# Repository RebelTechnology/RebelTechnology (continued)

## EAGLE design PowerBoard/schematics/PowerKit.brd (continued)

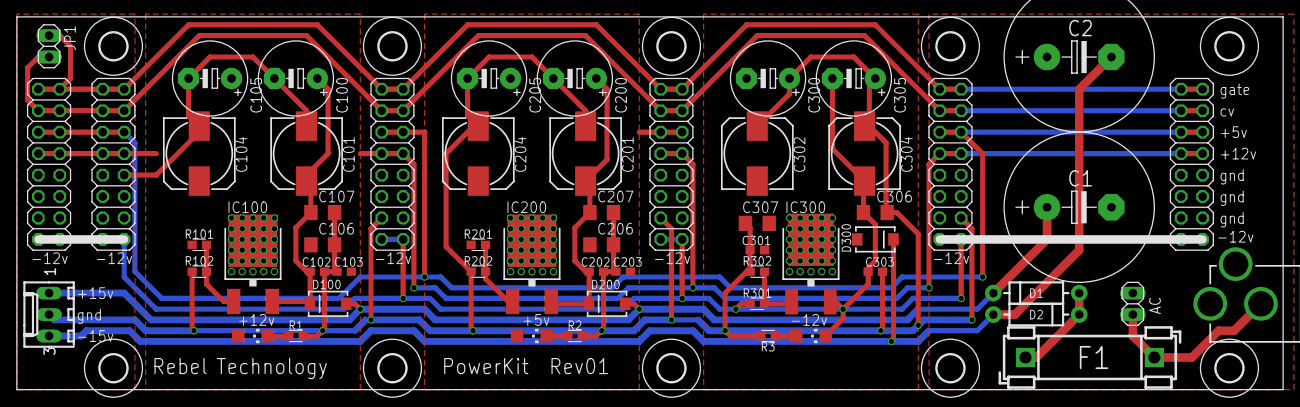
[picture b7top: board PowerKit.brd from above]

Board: 2 copper layers, 149.9 x 44.1 mm, 67 parts (0 on the bottom side), 19 nets.

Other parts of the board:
U$1, U$2, U$3, U$4, U$5, U$6, U$7, U$8, U$12, U$13: 3,2

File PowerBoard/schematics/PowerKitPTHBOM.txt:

Partlist exported from D:/Drive/Work/Rebel/ProjectFiles/RebelTechnology/PowerBoard/schematics/PowerKitPTH.sch at 14/04/2015 16:49:12

Qty Value            Device           Package            Parts                                                Description                                         
3                    LED3MM           LED3MM             LED1, LED2, LED3                                     LED                                                 
2                    PINHD-1X2        1X02               AC, JP1                                              PIN HEADER                                          
1                    POWER_JACKPTH    POWER_JACK_PTH     J1                                                   Power Jack                                          
6   100n             C-EU050-025X075  C050-025X075       C101, C103, C201, C203, C301, C303                   CAPACITOR, European symbol                          
9   10u              CPOL-EUE2.5-6    E2,5-6             C100, C102, C104, C200, C202, C204, C300, C302, C304 POLARIZED CAPACITOR, European symbol                
3   1N4004           1N4004           DO41-10            D100, D200, D300                                     DIODE                                               
2   1N5404           DIODE1N4001      DIODE-1N4001       D1, D2                                               Diode                                               
1   1k               R-EU_0204/7      0204/7             R202                                                 RESISTOR, European symbol                           
1   1k               R-EU_0207/7      0207/7             R2                                                   RESISTOR, European symbol                           
2   1k91             R-EU_0204/7      0204/7             R102, R302                                           RESISTOR, European symbol                           
1   22-27-2031-03    22-27-2031-03    6410-03            X1                                                   CONNECTOR                                           
1   2200u            CPOL-EUE7.5-18   E7,5-18            C2                                                   POLARIZED CAPACITOR, European symbol                
2   220R             R-EU_0204/7      0204/7             R101, R301                                           RESISTOR, European symbol                           
2   2k               R-EU_0207/7      0207/7             R1, R3                                               RESISTOR, European symbol                           
1   330R             R-EU_0204/7      0204/7             R201                                                 RESISTOR, European symbol                           
1   337T             337T             TO220H             IC300                                                Negative VOLTAGE REGULATOR                          
1   4700u            CPOL-EUE7.5-18   E7,5-18            C1                                                   POLARIZED CAPACITOR, European symbol                
1   FUSEBLANK_5X20MM FUSEBLANK_5X20MM FUSE_HOLDER_5X20MM F1                                                   Fuse                                                
2   LM317MABT        LM317MABT        TO220L1            IC100, IC200                                         500 mA Adjustable Output Positive Voltage Regulator 
6   M08X2            M08X2            2X8                OUT, OUT1, OUT2, OUT3, OUT4, OUT5

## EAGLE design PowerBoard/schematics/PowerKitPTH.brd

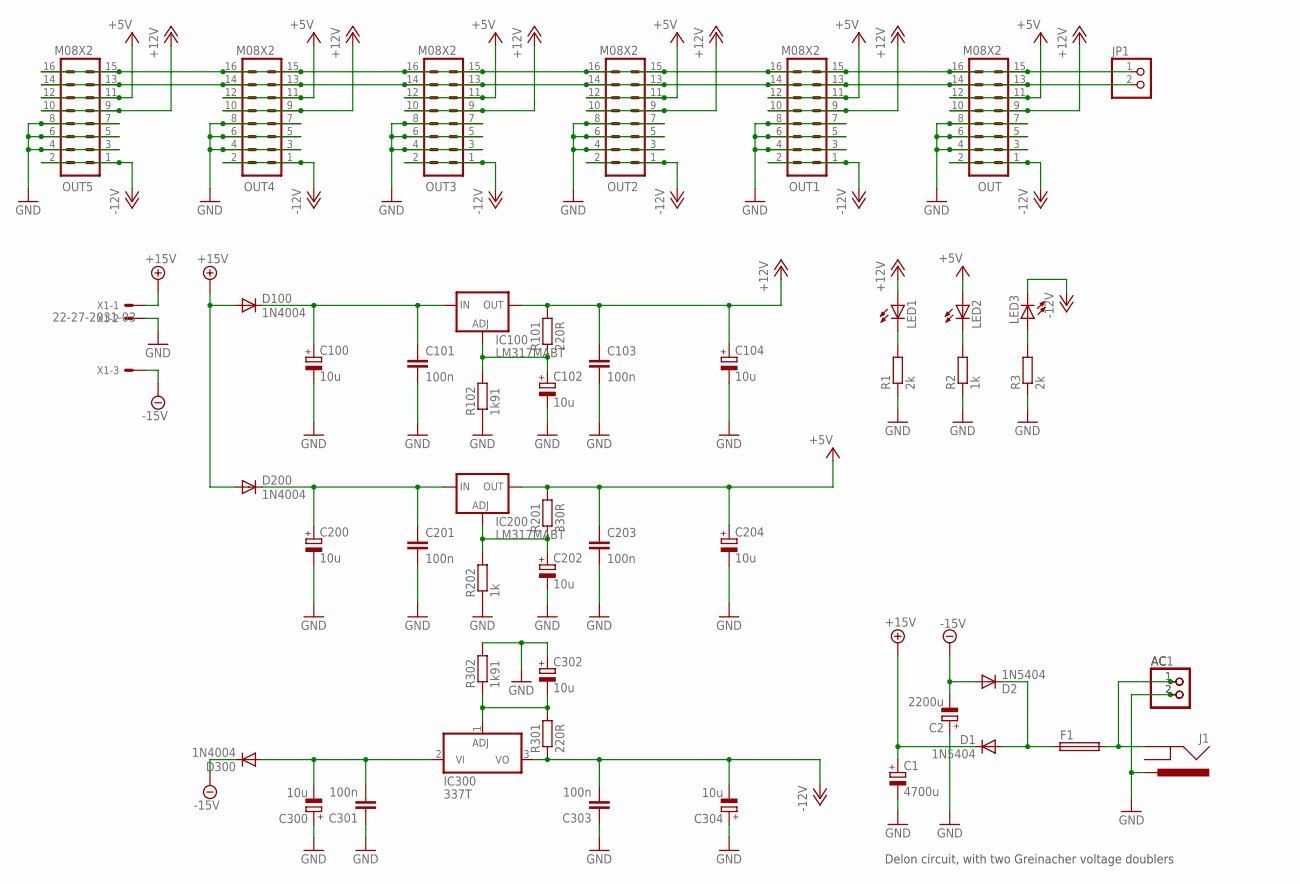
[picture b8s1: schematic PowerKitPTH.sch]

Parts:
AC, AC1: PINHD-1X2; 1X02
C1: 4700u; E7,5-18
C2: 2200u; E7,5-18
C100, C102, C104, C200, C202, C204, C300, C302, C304: 10u; E2,5-6
C101, C103, C201, C203, C301, C303: 100n; C050-025X075
D1, D2: 1N5404; DIODE-1N4001
D100, D200, D300: 1N4004; DO41-10
F1: SH22,5
IC100, IC200: LM317MABT; TO220L1
IC300: 337T; TO220H
J1: POWER_JACKPTH; POWER_JACK_PTH
JP1: PINHD-1X2; 1X02
LED1, LED2, LED3: LED3MM
OUT, OUT1, OUT2, OUT3, OUT4, OUT5: M08X2; 2X8
R1, R3: 2k; 0204/7
R2, R202: 1k; 0204/7
R101, R301: 220R; 0204/7
R102, R302: 1k91; 0204/7
R201: 330R; 0204/7
X1: 22-27-2031-03; 6410-03

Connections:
+5V: C203.1, C204.+, IC200.2 (OUT), LED2.A, OUT.11, OUT.12, OUT1.11, OUT1.12, OUT2.11, OUT2.12, OUT3.11, OUT3.12, OUT4.11, OUT4.12, OUT5.11, OUT5.12, R201.2
+12V: C103.1, C104.+, IC100.2 (OUT), LED1.A, OUT.9, OUT.10, OUT1.9, OUT1.10, OUT2.9, OUT2.10, OUT3.9, OUT3.10, OUT4.9, OUT4.10, OUT5.9, OUT5.10, R101.2
+15V: C1.+, D1.C, D100.A, D200.A, X1.1
-12V: C303.2, C304.-, IC300.3 (VO), LED3.K (C), OUT.1, OUT.2, OUT1.1, OUT1.2, OUT2.1, OUT2.2, OUT3.1, OUT3.2, OUT4.1, OUT4.2, OUT5.1, OUT5.2, R301.1
-15V: C2.-, D2.A, D300.C, X1.3
GND: AC.2, AC1.2, C1.-, C2.+, C100.-, C101.2, C102.-, C103.2, C104.-, C200.-, C201.2, C202.-, C203.2, C204.-, C300.+, C301.1, C302.+, C303.1, C304.+, J1.PWR, OUT.3, OUT.4, OUT.5, OUT.6, OUT.7, OUT.8, OUT1.3, OUT1.4, OUT1.5, OUT1.6, OUT1.7, OUT1.8, OUT2.3, OUT2.4, OUT2.5, OUT2.6, OUT2.7, OUT2.8, OUT3.3, OUT3.4, OUT3.5, OUT3.6, OUT3.7, OUT3.8, OUT4.3, OUT4.4, OUT4.5, OUT4.6, OUT4.7, OUT4.8, OUT5.3, OUT5.4, OUT5.5, OUT5.6, OUT5.7, OUT5.8, R1.1, R2.1, R3.1, R102.1, R202.1, R302.2, X1.2
unnamed: LED2.K (C), R2.2
unnamed: LED1.K (C), R1.2
unnamed: C102.+, IC100.1 (ADJ), R101.1, R102.2
unnamed: C202.+, IC200.1 (ADJ), R201.1, R202.2
unnamed: C302.-, IC300.1 (ADJ), R301.2, R302.1
unnamed: C300.-, C301.2, D300.A, IC300.2 (VI)
unnamed: C200.+, C201.1, D200.C, IC200.3 (IN)
unnamed: C100.+, C101.1, D100.C, IC100.3 (IN)
unnamed: LED3.A, R3.2
unnamed: JP1.2, OUT.13, OUT.14, OUT1.13, OUT1.14, OUT2.13, OUT2.14, OUT3.13, OUT3.14, OUT4.13, OUT4.14, OUT5.13, OUT5.14
unnamed: D1.A, D2.C, F1.1
unnamed: JP1.1, OUT.15, OUT.16, OUT1.15, OUT1.16, OUT2.15, OUT2.16, OUT3.15, OUT3.16, OUT4.15, OUT4.16, OUT5.15, OUT5.16
unnamed: AC.1, AC1.1, F1.2, J1.GND

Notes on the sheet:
Delon circuit, with two Greinacher voltage doublers

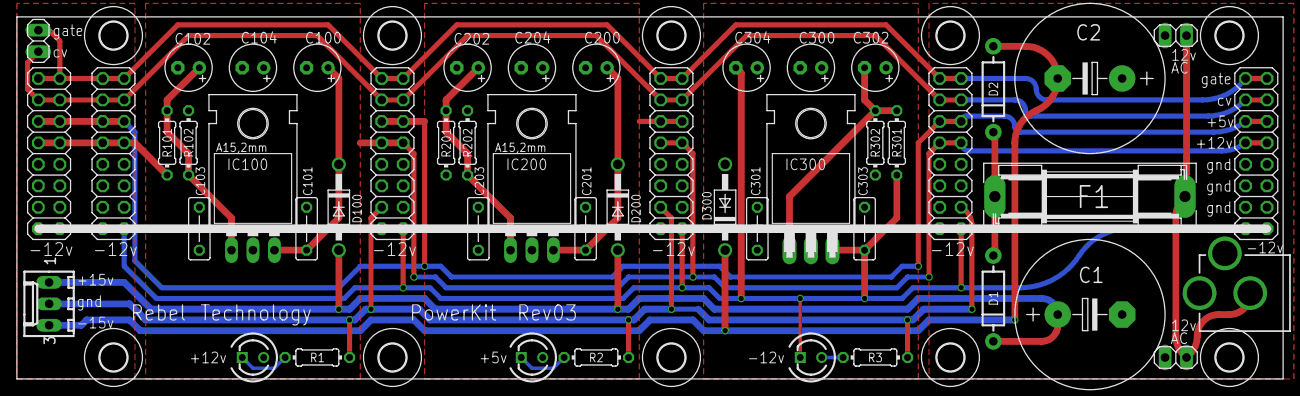
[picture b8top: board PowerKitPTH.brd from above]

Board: 2 copper layers, 149.9 x 42.9 mm, 59 parts (0 on the bottom side), 19 nets.

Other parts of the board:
U$1, U$2, U$3, U$4, U$5, U$6, U$7, U$8, U$12, U$13: 3,2

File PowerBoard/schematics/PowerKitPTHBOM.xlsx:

Qty | Value | Device | Package | Parts | Description
2 | 220R | R-EU_0204/7 | 0204/7 | R101, R301 | RESISTOR, European symbol
1 | 330R | R-EU_0204/7 | 0204/7 | R201 | RESISTOR, European symbol
1 | 1k | R-EU_0207/7 | 0207/7 | R2 | RESISTOR, European symbol
1 | 1k | R-EU_0204/7 | 0204/7 | R202 | RESISTOR, European symbol
2 | 1k91 | R-EU_0204/7 | 0204/7 | R102, R302 | RESISTOR, European symbol
2 | 2k | R-EU_0207/7 | 0207/7 | R1, R3 | RESISTOR, European symbol
3 | 1N4004 | 1N4004 | DO41-10 | D100, D200, D300 | DIODE
2 | 1N5404 | DIODE1N4001 | DIODE-1N4001 | D1, D2 | Diode
6 | 100n | C-EU050-025X075 | C050-025X075 | C101, C103, C201, C203, C301, C303 | CAPACITOR, European symbol
9 | 10u | CPOL-EUE2.5-6 | E2,5-6 | C100, C102, C104, C200, C202, C204, C300, C302, C304 | POLARIZED CAPACITOR, European symbol
1 | 2200u | CPOL-EUE7.5-18 | E7,5-18 | C2 | POLARIZED CAPACITOR, European symbol
1 | 4700u | CPOL-EUE7.5-18 | E7,5-18 | C1 | POLARIZED CAPACITOR, European symbol
2 | LM317MABT | LM317MABT | TO220L1 | IC100, IC200 | 500 mA Adjustable Output Positive Voltage Regulator
1 | 337T | 337T | TO220H | IC300 | Negative VOLTAGE REGULATOR
3 |  | LED3MM | LED3MM | LED1, LED2, LED3 | LED
1 | FUSEBLANK_5X20MM | FUSEBLANK_5X20MM | FUSE_HOLDER_5X20MM | F1 | Fuse
6 | M08X2 | M08X2 | 2X8 | OUT, OUT1, OUT2, OUT3, OUT4, OUT5
2 |  | PINHD-1X2 | 1X02 | AC, JP1 | PIN HEADER
1 |  | POWER_JACKPTH | POWER_JACK_PTH | J1 | Power Jack
1 | 22-27-2031-03 | 22-27-2031-03 | 6410-03 | X1 | CONNECTOR
